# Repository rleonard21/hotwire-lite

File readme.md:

# Hotwire Lite
## Overview
My [original hotwire controller design](https://github.com/rleonard21/hotwire-controller) was my first real embedded systems project and
had several shortcomings as a result. The goal of this "lite" project was to design and build
the cheapest version of the original project while significantly improving its performance.

(The [original project](https://github.com/rleonard21/hotwire-controller/blob/master/README.md) has some nice pictures of the project in action.)

## Observations
1. The power, LCD, and PID settings were never changed after finding the
right values.
2. The rotary encoder was a bit delicate when wearing gloves.
3. The circuit was erroneously running at 244Hz PWM and 14Hz PID rates and took several seconds to settle.

## Project Results
#### Product Costs
| Cost (single)     | Original Hotwire | Hotwire Lite |
|-------------------|------------------|--------------|
| PCB               | $5 (ALLPCB)      | $5 (PCBWay)  |
| Electrical        | ~$38             | $5.18        |
| Mechanical        | ~$20             | $0           |
| Total cost        | ~$63             | $10.18       |
| Bulk cost  (100)  | ?                | $3.71        |
| PCB assembly time | 1-1.5 hours      | <20 minutes  |
| Machining time    | 2-3 hours        | N/A          |

#### Ease of Manufacturing
| Manufacturing Ease | Original Hotwire | Hotwire Lite |
|--------------------|------------------|--------------|
| # SMD              | 33               | 19           |
| # PTH              | 8                | 0            |
| Screws             | Yes              | No           |
| Machining required | Yes              | No           |

#### Circuit Performance
| Performance            | Original Hotwire | Hotwire Lite       |
|------------------------|------------------|--------------------|
| Output accuracy @ 25W  | -4.6%            | 0.08%              |
| Settling time          | ~8 seconds       | milliseconds       |
| PWM frequency          | 244Hz            | 1024Hz             |
| Control loop frequency | 14Hz             | 1KHz               |
| Calibration            | No               | Yes                |
| Data output            | No               | Yes                |

## Filtering
The PID controller needs to know the average current running through the
wire to effectively control the power output. The output is really a square
wave, so there needs to be some filtering to find the average. The original
controller did this in hardware with an expensive and bulky RC filter network.
The new circuit performs this in a clever manner. Instead of free running the ADC
and measuring the entire signal, the ADC is trigged only on the rising edge of the 
PWM signal. Therefore, the ADC only ever measures the maximum current in the circuit.
Multiplying this number by the duty cycle results in the average current. 
This operation is be performed much faster than the old circuit (1KHz vs. 14Hz).

## Component Optimization
Being the first circuit I ever made, the original controller was
over-engineered a bit. It used expensive components with great specifications,
even if the circuit didn't really need it. The new controller uses the
right components, trading off unused performance for lower cost.

## UART Data Output Format
The circuit continuously streams its current and voltage measurements over UART at a 1MHz buad. 
The format of the data is a comma-separated list formatted like so: `voltage,current,power,duty_cycle`.
The units are `mV,mA,mW,%*1000`.

## Calibration 
### Calibration Interface
The circuit can be calibrated over UART using a very basic, lightweight interface. The user just needs
to send a three character command over the UART interface, which currently runs at 500k buad.

```
C00-C99: calibrate the voltage divider to account for resistor tolerance. C50 is for ideal resistors.
P00-P99: set the power output, where the two digit number is the output in watts (P15 = 15W output).
```
### Resistor Calibration Calculation
The resistor calibration is performed by measuring the true output voltage, reading the measured voltage over UART,
and performing the following calculation:

```c
resistor_divider = vcc_true / vcc_measured / 3
C_value = round(resistor_divider - 2.50, 2) * 100

calibration command = "C{C_value}"
```

Alternatively, manipulate the C value until the controller is outputting the correct power
to the desired accuracy.

#### Calibration Example:
```c
vcc_true = 13.993  // the voltage as measured by the multimeter
vcc_measured = 13.881  // the voltage as output over UART
resistor_divider = 13.993 / 13.881 / 3 = 3.024
C_value = round(3.024 - 2.50, 2) * 100 = 52

calibration command: "C52"
```
## Images

The assembled v1.0 hardware.

A close up of the v1.0 hardware while testing.

The four revisions of the hotwire controller project between 2018 (top) and 2022 (bottom).

The calibration station using a high power PCB resistor.

## References
[My original hotwire project](https://github.com/rleonard21/hotwire-controller)

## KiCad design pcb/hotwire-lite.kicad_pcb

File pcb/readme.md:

# Hardware Design
## Overview
## Versions
### v0.1
The purpose of this version is to validate the ability to implement the
desired algorithm on the ATTiny402, which has limited SRAM and flash memory.
Common parts with pre-existing KiCad symbols were used with little regard
for optimization.

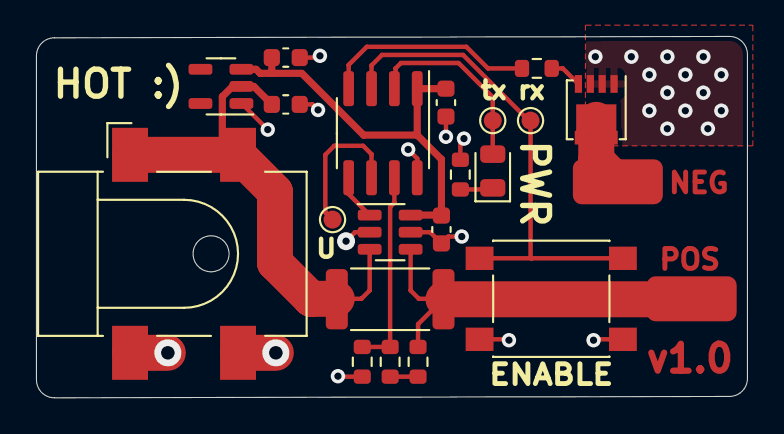
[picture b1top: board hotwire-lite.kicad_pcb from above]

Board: 2 copper layers, 39.5 x 20.1 mm, 22 parts (0 on the bottom side), 14 nets.

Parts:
C1, C2: 1uF; C_0603_1608Metric
C3, C4: 0.1uF; C_0603_1608Metric
D1: LED; LED_0805_2012Metric
J1: Barrel_Jack_Switch_Pin3Ring; BarrelJack_CLIFF_FC681465S_SMT_Horizontal
J2: WIRE+; wire_solder_pad
J3: WIRE-; wire_solder_pad
Q1: SiRA18ADP; Vishay_PowerPAK_1212-8_Single
R1, R2, R3: 10k; R_0603_1608Metric
R4, R5: 220; R_0603_1608Metric
R6: 0.050; R_2512_6332Metric
SW1: SW_Push; SW_SPST_PTS645
TP1, TP2, TP3: TestPoint; TestPoint_Pad_D1.0mm
U1: NCP716; SOT-23-5
U2: ATtiny402-SS; SOIC-8_3.9x4.9mm_P1.27mm
U3: INA180A1; SOT-23-6

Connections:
+5V: C2.1, C3.2, C4.2, U1.3 (VOUT), U2.1 (VCC), U3.6 (V+)
/UPDI: TP1.1, U2.6 (~RESET/PA0)
/current_sense: U2.5 (PA2), U3.1
/pwm_output: R5.1, U2.4 (PA1)
/rx_button: SW1.1, TP2.1, U2.3 (PA7)
/tx_led: D1.2 (A), TP3.1, U2.2 (PA6)
/vin: C1.1, J1.1, R6.1, U1.2 (VIN), U3.3 (+)
/voltage_sense: R2.2, R3.1, U2.7 (PA3)
/wire_neg: J3.1, Q1.5 (D)
/wire_pos: J2.1, R1.1, R6.2, U3.4 (-)
GND: C1.2, C2.2, C3.1, C4.1, J1.2, J1.3, Q1.1 (S), Q1.2 (S), Q1.3 (S), R3.2, R4.2, SW1.2, U1.1 (GND), U2.8 (GND), U3.2 (GND), U3.5 (REF)
unnamed: D1.1 (K), R4.1
unnamed: Q1.4 (G), R5.2
unnamed: R1.2, R2.1

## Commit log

2022-01-30 initial
2022-01-30 added time analysis of skipping average
2022-01-30 jupyter notebook
2022-01-31 starting source
2022-01-31 implemented the skipping average in C
2022-01-31 minor changes to SA
2022-02-01 added some optimizations, saved about ~150 bytes in compiled size for SA filter
2022-02-02 started v0.1 test hardware
2022-02-02 readme
2022-02-10 update ignore
2022-02-10 updated pcb
2022-02-18 added notebook for shunt amplifier
2022-03-01 Added working directory
2022-04-13 Power measure implementation
    Firmware now successfully measures power and controls output via PID.
2022-04-17 added some printing for v0.1.0
2022-04-19 v0.1.0 files were in wrong directory
2022-04-19 removed files in wrong spot
2022-04-19 removed image in wrong spot
2022-04-19 removed constant debug from main
2022-04-19 added new v1.0 hardware design
2022-04-19 v1.0 hardware
2022-04-19 exported v1.0 for order
2022-04-21 EEPROM implementation
    * Added nonvolatile memory saving for calibration and power setting
    * Fixed UART input reliability
2022-04-21 changed resistor values
2022-04-28 Updated to v1.0 hardware
    + removed unused code
    + fixed calibration erase on reflash problem
2022-04-28 added images
2022-04-28 fixed image links
2022-04-28 removed unused src
2022-04-28 added tables to readme
2022-04-28 added headers
2022-04-28 updated performance spec
2023-04-15 Delete dsp directory
    Skipping average functions went unused in favor of a better sampling configuration.
